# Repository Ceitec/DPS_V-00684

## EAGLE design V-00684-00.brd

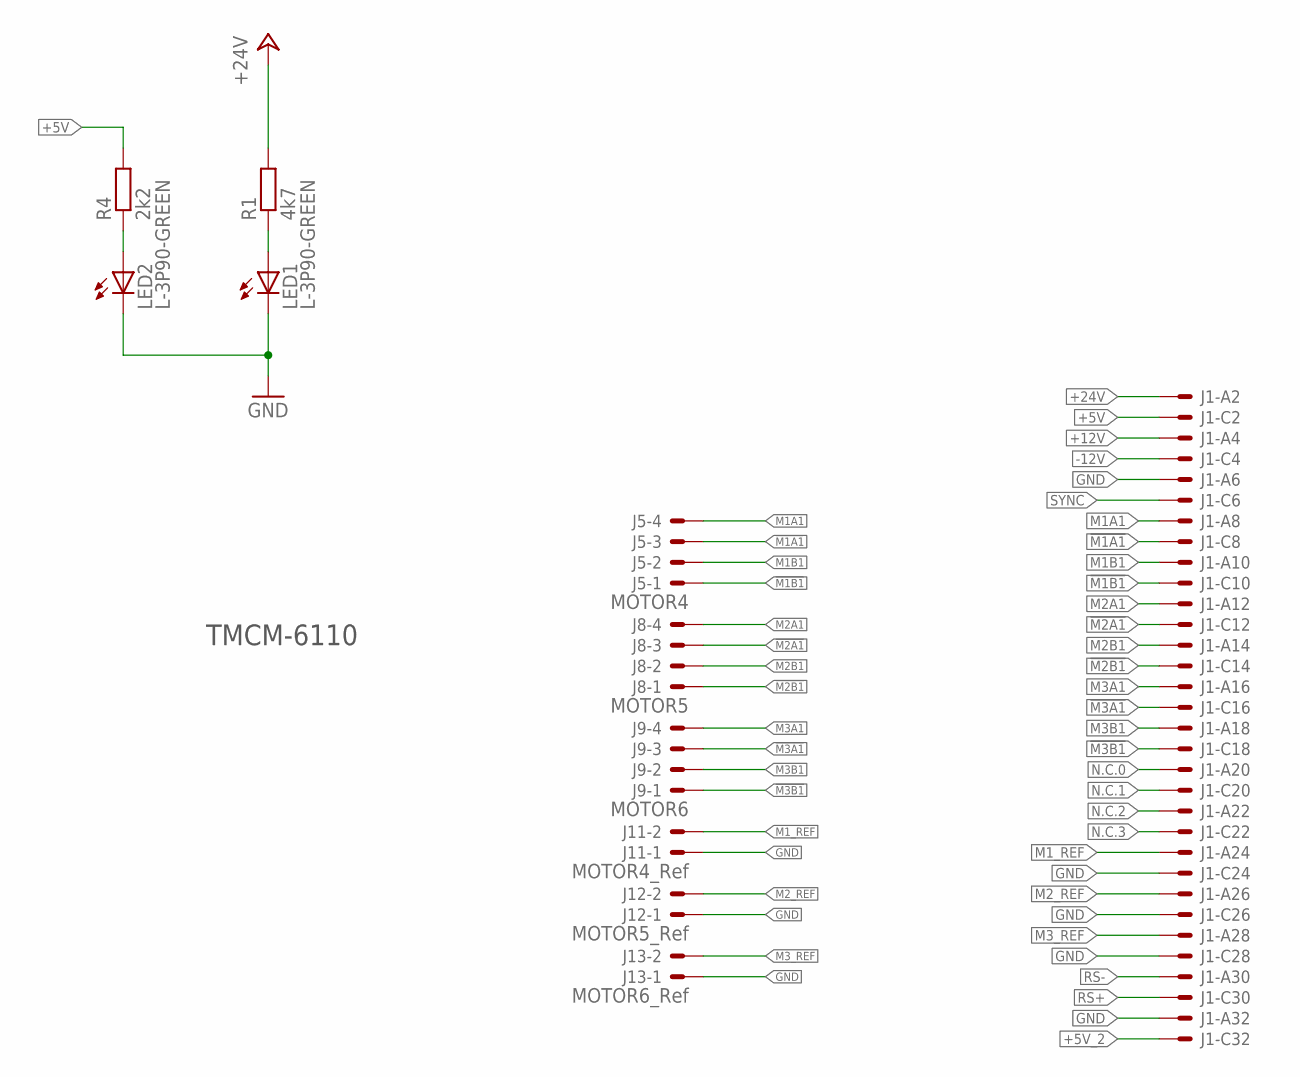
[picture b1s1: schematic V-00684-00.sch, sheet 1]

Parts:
J1: VG32SP; VG32P
J5: MOTOR4; 7395-04
J8: MOTOR5; 7395-04
J9: MOTOR6; 7395-04
J11: MOTOR4_Ref; 7395-02
J12: MOTOR5_Ref; 7395-02
J13: MOTOR6_Ref; 7395-02
LED1, LED2: L-3P90-GREEN; L-3P90
R1: 4k7; R1206
R4: 2k2; R1206

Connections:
!M1A1: J1.C8 (MS), J5.3
!M1B1: J1.C10 (MS), J5.1
!M2A1: J1.C12 (MS), J8.3
!M2B1: J1.C14 (MS), J8.1
!M3A1: J1.C16 (MS), J9.3
!M3B1: J1.C18 (MS), J9.1
+5V: J1.C2 (MS), R4.2
+5V_2: J1.C32 (MSV)
+12V: J1.A4 (MS)
+24V: J1.A2 (MS), R1.2
-12V: J1.C4 (MS)
GND: J1.A6 (MS), J1.A32 (MS), J1.C24 (MS), J1.C26 (MS), J1.C28 (MS), J11.1, J12.1, J13.1, LED1.K (C), LED2.K (C)
M1A1: J1.A8 (MS), J5.4
M1B1: J1.A10 (MS), J5.2
M1_REF: J1.A24 (MS), J11.2
M2A1: J1.A12 (MS), J8.4
M2B1: J1.A14 (MS), J8.2
M2_REF: J1.A26 (MS), J12.2
M3A1: J1.A16 (MS), J9.4
M3B1: J1.A18 (MS), J9.2
M3_REF: J1.A28 (MS), J13.2
unnamed: LED1.A, R1.1
unnamed: LED2.A, R4.1
N.C.0: J1.A20 (MS)
N.C.1: J1.C20 (MS)
N.C.2: J1.A22 (MS)
N.C.3: J1.C22 (MS)
RS+: J1.C30 (MS)
RS-: J1.A30 (MS)
SYNC: J1.C6 (MS)

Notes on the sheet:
TMCM-6110

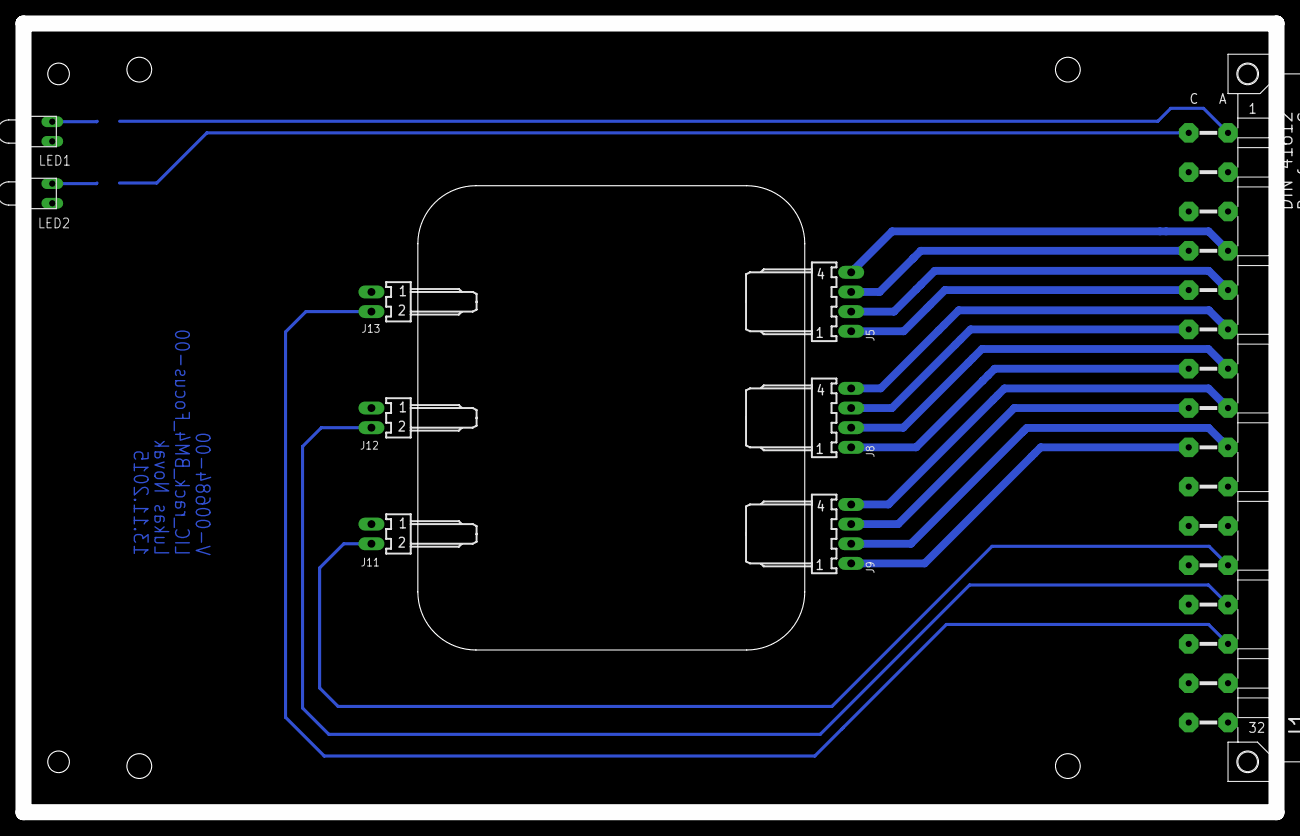
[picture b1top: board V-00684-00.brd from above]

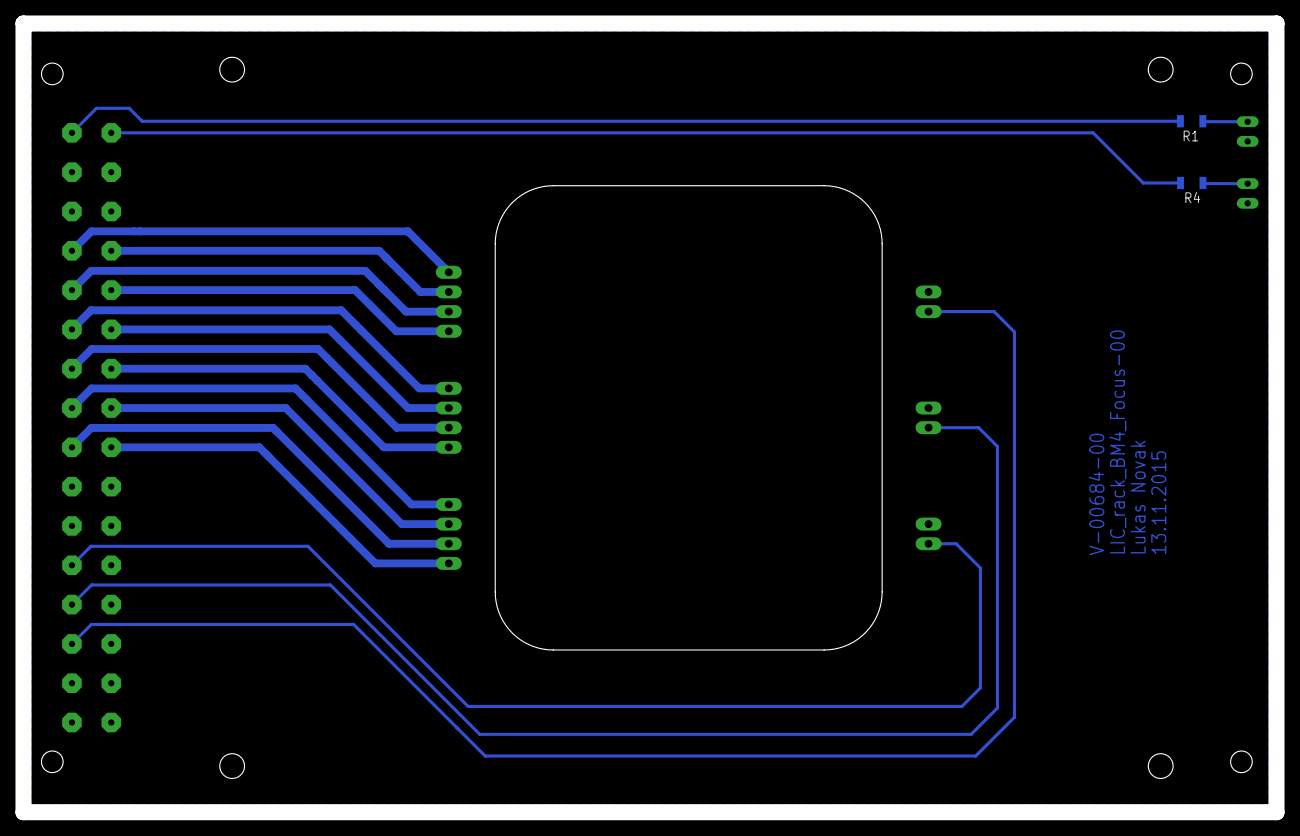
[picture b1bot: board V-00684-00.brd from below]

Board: 2 copper layers, 162.0 x 102.0 mm, 11 parts (2 on the bottom side), 20 nets.

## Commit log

2015-11-10 :tada: Added .gitattributes & .gitignore files
2015-11-10 Prvotní verze
2015-11-30 Save
